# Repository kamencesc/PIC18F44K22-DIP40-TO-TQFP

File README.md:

#UNTESTED

# PIC18F44K22 DIP40 to TQFP44

An adapter to use TQFP44 format of PIC18F44K22 into a DIP40 socket.

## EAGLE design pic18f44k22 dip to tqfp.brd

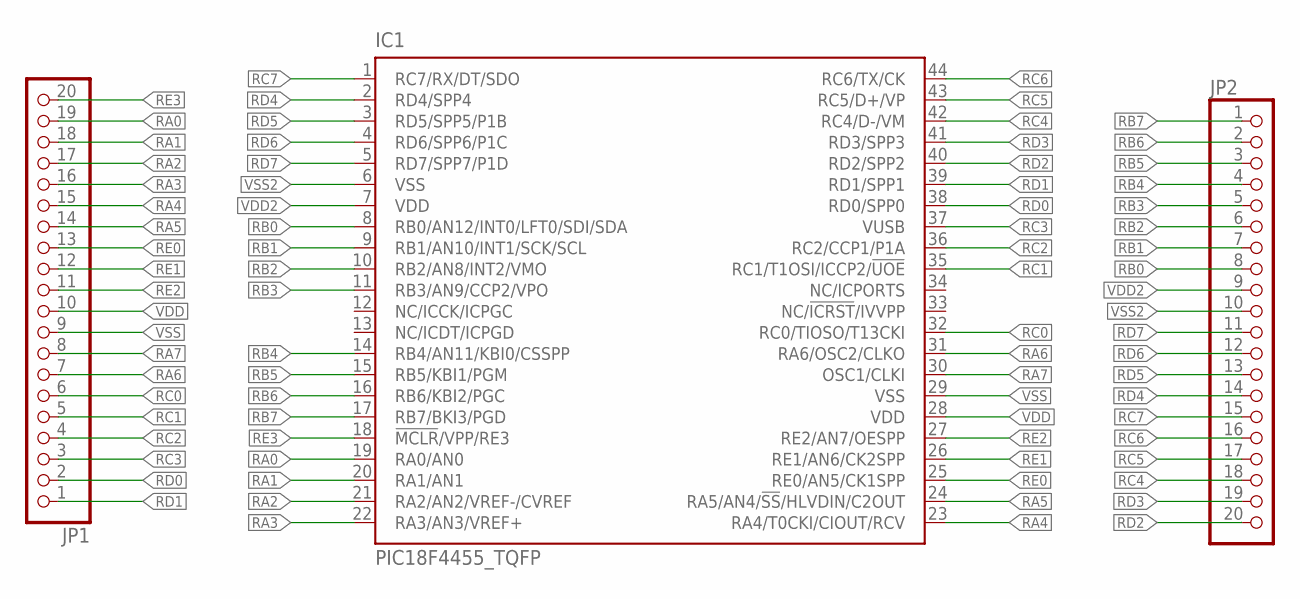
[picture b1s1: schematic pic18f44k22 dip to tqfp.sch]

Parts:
IC1: PIC18F4455_TQFP; TQFP44
JP1, JP2: PINHD-1X20_2.54-SMD; 1X20SMD

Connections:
RA0: IC1.19 (RA0/AN0), JP1.19
RA1: IC1.20 (RA1/AN1), JP1.18
RA2: IC1.21 (RA2/AN2/VREF-/CVREF), JP1.17
RA3: IC1.22 (RA3/AN3/VREF+), JP1.16
RA4: IC1.23 (RA4/T0CKI/CIOUT/RCV), JP1.15
RA5: IC1.24 (RA5/AN4/!SS!/HLVDIN/C2OUT), JP1.14
RA6: IC1.31 (RA6/OSC2/CLKO), JP1.7
RA7: IC1.30 (OSC1/CLKI), JP1.8
RB0: IC1.8 (RB0/AN12/INT0/LFT0/SDI/SDA), JP2.8
RB1: IC1.9 (RB1/AN10/INT1/SCK/SCL), JP2.7
RB2: IC1.10 (RB2/AN8/INT2/VMO), JP2.6
RB3: IC1.11 (RB3/AN9/CCP2/VPO), JP2.5
RB4: IC1.14 (RB4/AN11/KBI0/CSSPP), JP2.4
RB5: IC1.15 (RB5/KBI1/PGM), JP2.3
RB6: IC1.16 (RB6/KBI2/PGC), JP2.2
RB7: IC1.17 (RB7/BKI3/PGD), JP2.1
RC0: IC1.32 (RC0/TIOSO/T13CKI), JP1.6
RC1: IC1.35 (RC1/T1OSI/ICCP2/!UOE), JP1.5
RC2: IC1.36 (RC2/CCP1/P1A), JP1.4
RC3: IC1.37 (VUSB), JP1.3
RC4: IC1.42 (RC4/D-/VM), JP2.18
RC5: IC1.43 (RC5/D+/VP), JP2.17
RC6: IC1.44 (RC6/TX/CK), JP2.16
RC7: IC1.1 (RC7/RX/DT/SDO), JP2.15
RD0: IC1.38 (RD0/SPP0), JP1.2
RD1: IC1.39 (RD1/SPP1), JP1.1
RD2: IC1.40 (RD2/SPP2), JP2.20
RD3: IC1.41 (RD3/SPP3), JP2.19
RD4: IC1.2 (RD4/SPP4), JP2.14
RD5: IC1.3 (RD5/SPP5/P1B), JP2.13
RD6: IC1.4 (RD6/SPP6/P1C), JP2.12
RD7: IC1.5 (RD7/SPP7/P1D), JP2.11
RE0: IC1.25 (RE0/AN5/CK1SPP), JP1.13
RE1: IC1.26 (RE1/AN6/CK2SPP), JP1.12
RE2: IC1.27 (RE2/AN7/OESPP), JP1.11
RE3: IC1.18 (!MCLR!/VPP/RE3), JP1.20
VDD: IC1.28 (VDD), JP1.10
VDD2: IC1.7 (VDD), JP2.9
VSS: IC1.29 (VSS), JP1.9
VSS2: IC1.6 (VSS), JP2.10

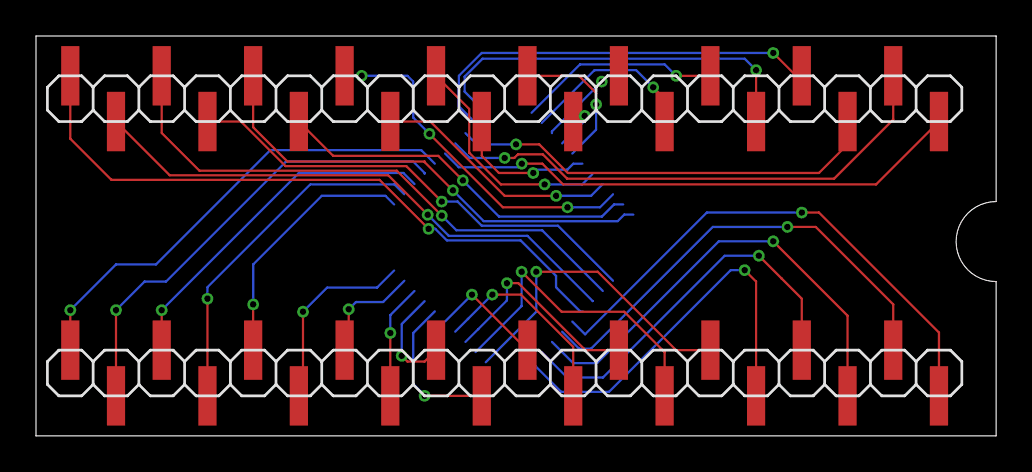
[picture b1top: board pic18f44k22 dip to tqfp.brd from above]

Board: 2 copper layers, 53.3 x 22.2 mm, 3 parts (1 on the bottom side), 40 nets.

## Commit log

2019-05-24 SCH and BRD
    First version, untested.
    4 pins of PIC18F44K22 are NC
2019-05-24 Add files via upload
    Adjustments...
2019-05-24 Add files via upload
    Files has been renamed, some little changes on traces.
2019-05-24 Delete pic18f44k22 dip to rqf.sch
    Remove old one
2019-05-24 Delete pic18f44k22 dip to rqf.brd
    Remove old one
